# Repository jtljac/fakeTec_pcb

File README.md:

# fakeTec_pcb
My personal modification of the fakeTec, a low-cost nRF52 device with the form-factor of the Heltec v2, v3, & v4 devices 
compatible with [Meshtastic](https://meshtastic.org/)®.

This design is specifically based off of [Šimon Hořánek's](https://github.com/ShimonHoranek) 
[fakeTec V5 Rev. B](https://github.com/gargomoma/fakeTec_pcb/issues/24), licensed under 
[CERN-OHL-P-2.0](https://choosealicense.com/licenses/cern-ohl-p-2.0/).

Further inspiration has been taken from [Brian's Fork, the roTec](https://github.com/mofosyne/roTec_pcb), an alternative
board with greatly expanded wiring options and extra on-board guidence.

# Pictures
| Front                               | Back                              |
|:------------------------------------|:----------------------------------|
|  |  |

# Schematic
<details>
<summary>Schematic and component list</summary>
Note this list is for the v5.5.1

| Component Ref | Value     |
|:------------- |:--------- |
| C1, C2        | 100nf     |
| Q1, Q2, Q3    | AO3400A*  |
| R1, R2, R3    | 10K       |
| R4            | 680K      |
| R5            | 1M        |
| U1            | XB8089D0  |
| U2            | HT-RA62   |
| U3            | nice!nano |

\* Can be any SOT-23 logic level MOSFET that supports atleast 3v
</details>

## Features
- Small size based on Heltec v3: You can use the same cases!
- Lora with Heltec's HT-RA62
- Uses a [n!cenano](https://nicekeyboards.com/nice-nano/) or 
  [NRF52840 ProMicro](https://github.com/joric/nrfmicro/wiki/Alternatives#supermini-nrf52840l)
- BMS For low voltage cutout to prevent LiPo Overdraining
- Battery level sensing
- JST PH2.0mm connector for batteries
- I2C side ports ready to connect an OLED SSD1306 screen.
- Pads for connecting an encoder for canned messages
- A pad exposing P1.06 (38) for misc use
- Pads for connecting a serial GPS module
- MOSFETs for switching high current components
- 2mm mounting holes
- Mostly clear edges for mounting

## Modifications from fakeTec V5 Rev. B
- Cleaned up schematic
  - Changed Pins representing sides of MCUs to symbols fully representing said MCU
  - Changed labels to my preferred naming scheme
- Setup netclasses
- Shifted pads `P1.01`, `P1.02`, and `P1.07` to where I'm pretty sure they're supposed to be
  - I also added two sets as the NRF ProMicro and the Nice!Nano appear to have them in different places.
- Removed jumper for BMS
  - I will always install a BMS
- Removed jumper for GPS/FET1 Drain to FET1
  - Only one will be connected at a time, probably no difference if this is permanently connected to both
- Switched mosfets to AO3400A
  - I already have these and they're a drop in replacement
- Changed all resistors and Capacitors to 805 sized
  - I already have all the resistors in this size
- Removed debouncing capacitors and pull-up resistors from the buttons
  - [User mofosyne](https://github.com/mofosyne) provided evidence that it is unnecessary 
    [here](https://github.com/gargomoma/fakeTec_pcb/issues/64)
- Added ground pads to rotary encoder pads
- Added access to P1.06 for misc usage next to rotary encoder pads
- Changed battery connector to a JST PH-2.0mm
  - PH-2.0mm are also apparently more reliable
- Removed lots of silkscreen text
  - Don't need values or component names, just component references
  - Most of it was overlapping
- Moved BMS to side
  - Keeps it out the way of the battery connector
- Added a lot more stitching between front and back ground planes
- Removed vias from on top of silkscreen and off of pads
- Attempted to reduce layer crossings

# Firmware

| Version      | Lora Modules                     | Official Repo link                                                                                                                                          | Unofficial Repo link                                                                                                                                                                |
|:-------------|:---------------------------------|:------------------------------------------------------------------------------------------------------------------------------------------------------------|:------------------------------------------------------------------------------------------------------------------------------------------------------------------------------------|
| With TCXO    | EByte E22/E220-xxxM-22S/HT-RA62  | <a href="https://github.com/meshtastic/firmware/tree/master/variants/nrf52840/diy/nrf52_promicro_diy_tcxo" target="_blank">Official repo - With TCXO</a>    | <a href="https://github.com/mrekin/MeshtasticCustomBoards/tree/main/firmware/variants/nrf52840/diy/promicro_diy_m" target="_blank">With TCXO</a> @mrekin/MeshtasticCustomBoards     |
| Without TCXO | EByte E22/E220-xxxMM-22S/RA-01SH | <a href="https://github.com/meshtastic/firmware/tree/master/variants/nrf52840/diy/nrf52_promicro_diy_xtal" target="_blank">Official repo - Without TCXO</a> | <a href="https://github.com/mrekin/MeshtasticCustomBoards/tree/main/firmware/variants/nrf52840/diy/promicro_diy_mm" target="_blank">Without TCXO</a> @mrekin/MeshtasticCustomBoards |

> If you don't want to build your own image use <a href="https://flasher.meshtastic.org/" target="_blank">the official web flasher</a>. Select the `NRF52 Pro-micro DIY` under `Community Supported Devices` as your target device.

# Device Setup
After you've set up your device, there are a few things you can do in the config to tune it

## Battery ADC Multiplier
The default ADC multiplier for the DIY NRF52 Promicro firmware is slightly off at about `1.85`, due to this design using
a slightly differnt voltage divider, I found that mine is more accurate with a value of `1.68`.  
You should of course still tune yours further with https://meshtastic.org/docs/configuration/radio/power/#calibration-process-attribution

# Bill of materials
| Part                           | Source                                                                                                                                      | Note                                                                                                      |
|:-------------------------------|:--------------------------------------------------------------------------------------------------------------------------------------------|:----------------------------------------------------------------------------------------------------------|
| NRF52840 ProMicro or n!icenano | [AliExpress](https://www.aliexpress.com/item/1005006446457448.html)<br/> [niceKeyboards](https://nicekeyboards.com/nice-nano/#find-a-store) |[Please read it before buying red ProMicros](https://github.com/gargomoma/fakeTec_pcb/issues/30)           |
| HT-RA62                        | [Heltec](https://heltec.org/project/ht-ra62/)<br/> [AliExpress](https://www.aliexpress.com/item/1005005543917617.html)                      | I'd get it directly from heltec                                                                           |
| XB8089D0 BMS                   | [LCSC](https://www.lcsc.com/product-detail/C2760005.html)                                                                                   |                                                                                                           |
| 3x AO3400A MOSFETs             | [LCSC](https://www.lcsc.com/product-detail/C347475.html)<br/> [AliExpress](https://www.aliexpress.com/item/1005007115799728)                | Quite frankly, any logic level N-Channel MOSFET with a `SOT-23` footprint that takes at least 5v will do. |
| SMD JST PH2.0mm Socket         | [LCSC](https://www.lcsc.com/product-detail/C295747.html)<br/> [LCSC](https://www.lcsc.com/product-detail/C7429689.html)                     |                                                                                                           |
| SMD 805 Resistors              |                                                                                                                                             | You'll need 1x 1k, 3x 10K, 1x 680K, 1x 1M                                                                 |
| SMD 805 Ceramic Capacitors     |                                                                                                                                             | You'll need 2 x 100nF                                                                                     |
| 2x smd Button                  | [LCSC](https://www.lcsc.com/product-detail/C41427500.html)                                                                                  | You want something around 4 x 3 x 2                                                                       |
| OLED SSD1306 i2c (optional)    | [AliExpress](https://www.aliexpress.com/item/1005005970901119.html)                                                                         |                                                                                                           |
| Battery connection (optional)  | [AliExpress](https://www.aliexpress.com/item/1005002564191148.html)                                                                         | This is an example.                                                                                       |
| Glue Stick Sprint Antenna      | [AliExpress](https://www.aliexpress.com/item/1005008671071222.html)                                                                         |                                                                                                           |
| Antenna (Recommended           | [AliExpress](https://www.aliexpress.com/item/1005004607615001.html)                                                                         |                                                                                                           |
| Antenna pigtail (recommended)  | [AliExpress](https://www.aliexpress.com/item/4001287491018.html)                                                                            | It may underperformed with a cheap black pigtail.                                                         |
| PCB                            |                                                                                                                                             | Use your favourite company to get the PCB. I use [JLCPCB](https://jlcpcb.com/)                            |

# Troubleshooting
## Cannot write the firmware to the Microcontroller
It appears that many NRF ProMicros on AliExpress come with an older version of the bootloader which doesn't support
uf2 files that are larger than 512KB.
The steps to fix are detailed in [this github issue](https://github.com/meshtastic/firmware/issues/7091), of which were
taken from [this older FakeTec Guide](https://adrelien.com/blog/diy-meshtastic-how-to-build-your-own-meshtastic-device-with-faketec-pcb-nrf52840/#step-1-update-the-bootloader).  
They're also copied below for convenience:
1. Connect the node to your PC using a data cable
2. Put the node into DFU (Device Firmware Update) mode by shorting the GND and Reset pins once or twice, A new drive 
   should appear on your computer
3. Check the INFO_UF2.TXT file to determine your current bootloader version
4. Visit Adafruit's GitHub page for nRF52 Bootloader releases
5. Find the next release after your current version (you must update incrementally)
6. Download the nice_nano_bootloader-X.X.X.HEX and nice_nano_bootloader-X.X.X.UF2 files for your board
7. Drag and drop the .HEX file onto the drive first, then the .UF2 file
8. The device will disconnect and restart
9. Check the bootloader version again and repeat if necessary until you reach the latest version

My ProMicros arrived at version 6.0.0, and I only updated to 0.6.3 as it started working at that version and it looked
like a long process to go to the latest version.

## The Microcontroller isn't getting power/The microcontroller can't connect the battery/The microcontroller can't connect to the LoRa module/The buttons don't work
The micro controller is pretty difficult to solder to the pads through the through holes, it took me many attempts to
get it right.

Make sure you check each connection using a multimeter before you decide you've finished soldering.

If you're really struggling, you can use a fine file to turn the through holes into castellated edges.
 
Be careful though, fibreglass shards are not good for your lungs

## The battery isn't working
Double check which way round your battery connector is wired. The batteries I bought were wired the opposite way to the
connector on the board.

# About Meshtastic
[Meshtastic](https://meshtastic.org/)® is a registered trademark of Meshtastic LLC. Meshtastic software components are released under various licenses, see github for details.

# Disclaimer
No warranty is provided.
You use it at your own risk and take the responsibility upon yourself.

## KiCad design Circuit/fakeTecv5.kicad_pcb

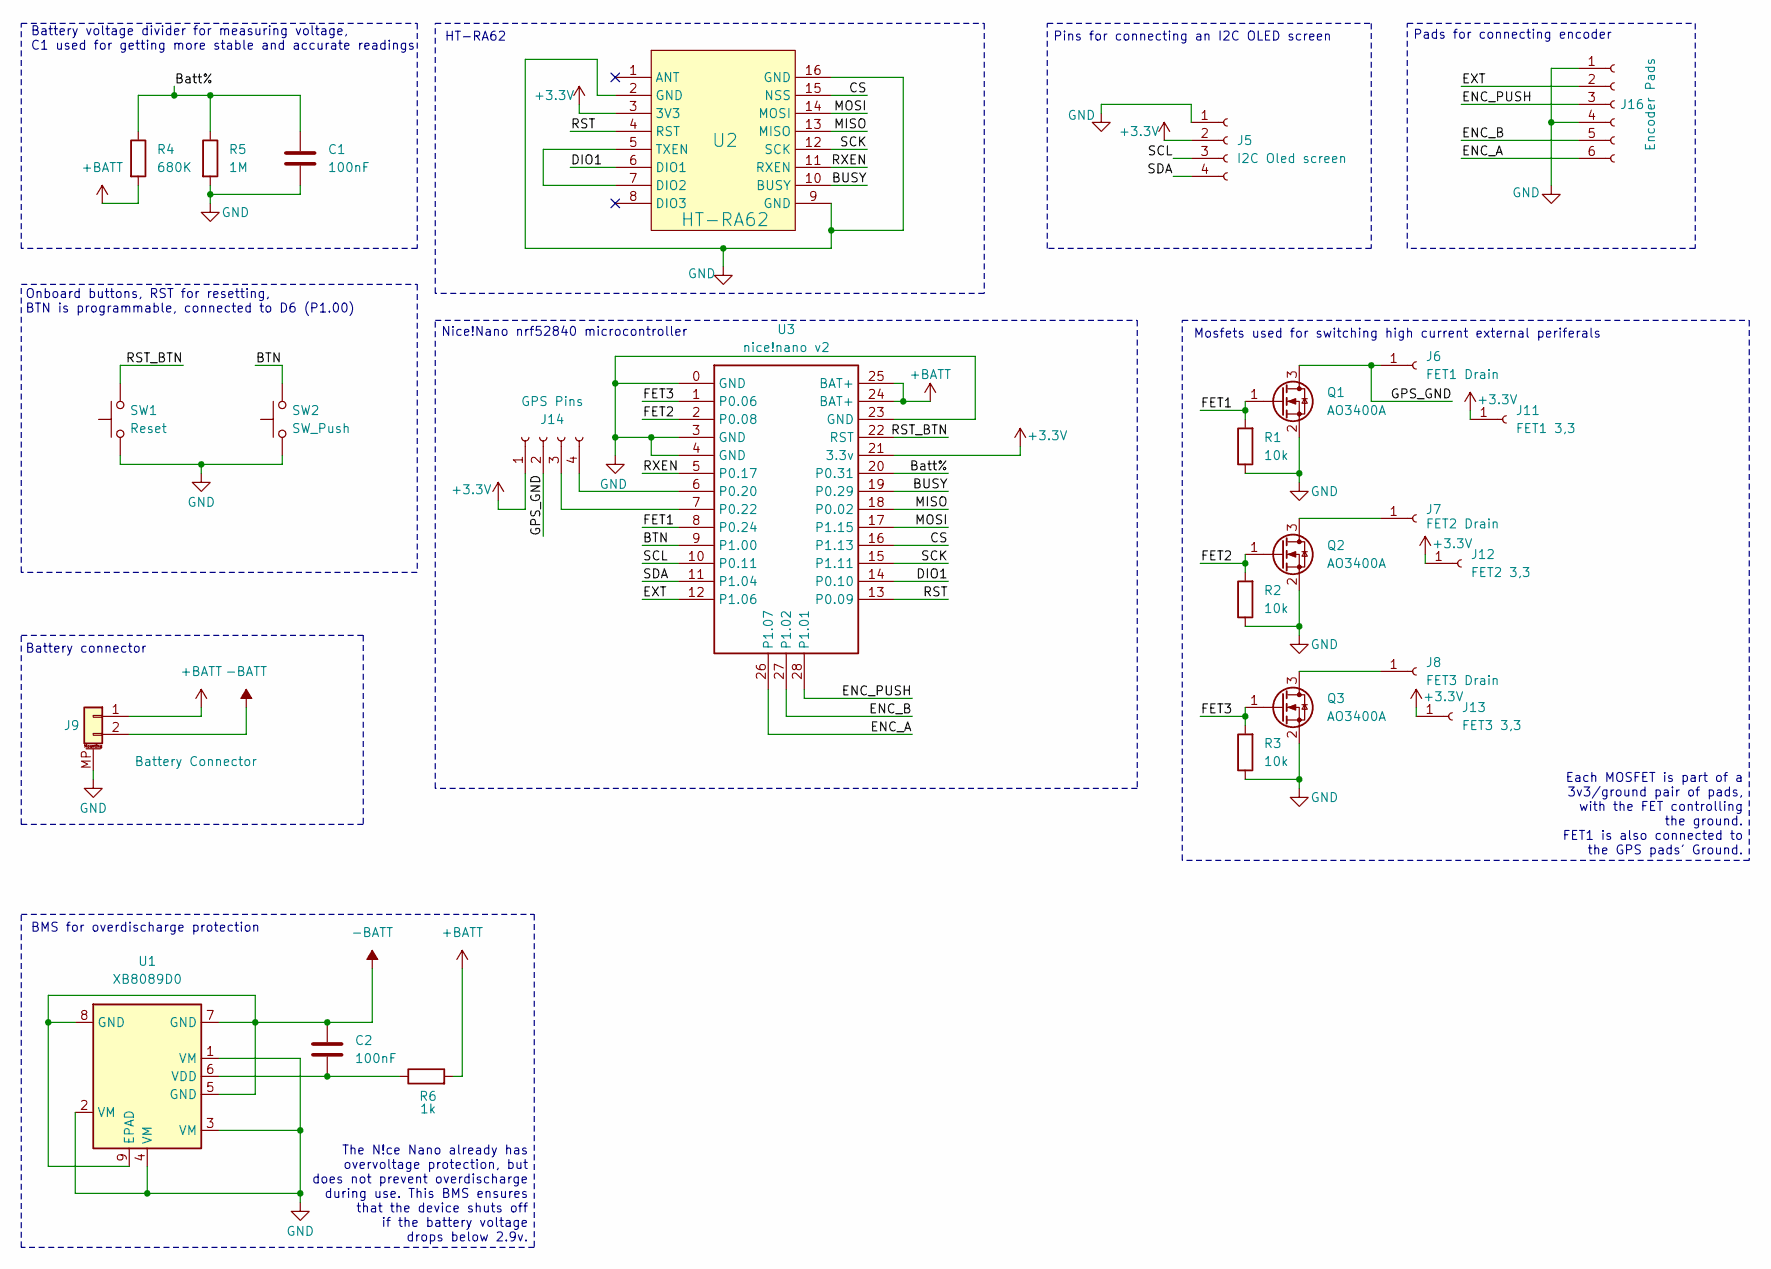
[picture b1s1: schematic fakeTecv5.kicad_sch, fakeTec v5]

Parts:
C1, C2: 100nF; C_0805_2012Metric_Pad1.18x1.45mm_HandSolder
J5: I2C Oled screen; PinHeader_1x04_P2.54mm_Vertical
J6: FET1 Drain; SMD_PAD_1x01
J7: FET2 Drain; SMD_PAD_1x01
J8: FET3 Drain; SMD_PAD_1x01
J9: Battery Connector; JST_PH_S2B-PH-SM4-TB_1x02-1MP_P2.00mm_Horizontal
J11: FET1 3,3; SMD_PAD_1x01
J12: FET2 3,3; SMD_PAD_1x01
J13: FET3 3,3; SMD_PAD_1x01
J14: GPS Pins; SMD_PAD_1x04
J16: Encoder Pads; SMD_PAD_1x06
Q1, Q2, Q3: AO3400A; SOT-23_Handsoldering
R1, R2, R3: 10k; R_0805_2012Metric_Pad1.20x1.40mm_HandSolder
R4: 680K; R_0805_2012Metric_Pad1.20x1.40mm_HandSolder
R5: 1M; R_0805_2012Metric_Pad1.20x1.40mm_HandSolder
R6: 1k; R_0805_2012Metric_Pad1.20x1.40mm_HandSolder
SW1: Reset; SW_Push_SPST_NO_Alps_SKRK
SW2: SW_Push; SW_Push_SPST_NO_Alps_SKRK
U1: XB8089D0; SOIC-8-1EP_3.9x4.9mm_P1.27mm_EP2.41x3.3mm
U2: HT-RA62
U3: nice!nano v2; NICE!NANO V2_2 SMD

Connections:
+3.3V: J5.2, J11.1, J12.1, J13.1, J14.1, U2.3 (3V3), U3.21 (3.3v)
+BATT: J9.1, R4.2, R6.2, U3.24 (BAT+), U3.25 (BAT+)
-BATT: C2.1, J9.2, U1.5 (GND), U1.7 (GND), U1.8 (GND), U1.9 (EPAD)
/BTN: SW2.2, U3.9 (P1.00)
/BUSY: U2.10 (BUSY), U3.19 (P0.29)
/Batt%: C1.1, R4.1, R5.1, U3.20 (P0.31)
/CS: U2.15 (NSS), U3.16 (P1.13)
/DIO1: U2.6 (DIO1), U3.14 (P0.10)
/ENC_A: J16.6, U3.26 (P1.07)
/ENC_B: J16.5, U3.27 (P1.02)
/ENC_PUSH: J16.3, U3.28 (P1.01)
/EXT: J16.2, U3.12 (P1.06)
/FET1: Q1.1 (G), R1.2, U3.8 (P0.24)
/FET2: Q2.1 (G), R2.2, U3.2 (P0.08)
/FET3: Q3.1 (G), R3.2, U3.1 (P0.06)
/GPS_GND: J6.1, J14.2, Q1.3 (D)
/MISO: U2.13 (MISO), U3.18 (P0.02)
/MOSI: U2.14 (MOSI), U3.17 (P1.15)
/RST: U2.4 (RST), U3.13 (P0.09)
/RST_BTN: SW1.2, U3.22 (RST)
/RXEN: U2.11 (RXEN), U3.5 (P0.17)
/SCK: U2.12 (SCK), U3.15 (P1.11)
/SCL: J5.3, U3.10 (P0.11)
/SDA: J5.4, U3.11 (P1.04)
GND: C1.2, J5.1, J9.MP (MountPin), J16.1, J16.4, Q1.2 (S), Q2.2 (S), Q3.2 (S), R1.1, R2.1, R3.1, R5.2, SW1.1, SW2.1, U1.1 (VM), U1.2 (VM), U1.3 (VM), U1.4 (VM), U2.2 (GND), U2.9 (GND), U2.16 (GND), U3.0 (GND), U3.3 (GND), U3.4 (GND), U3.23 (GND)
unnamed: J7.1, Q2.3 (D)
unnamed: J8.1, Q3.3 (D)
unnamed: J14.3, U3.7 (P0.22)
unnamed: J14.4, U3.6 (P0.20)
unnamed: C2.2, R6.1, U1.6 (VDD)
unnamed: U2.5 (TXEN), U2.7 (DIO2)

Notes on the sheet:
Nice!Nano nrf52840 microcontroller
Pads for connecting encoder
Mosfets used for switching high current external periferals
The N!ce Nano already has overvoltage protection, but does not prevent overdischarge during use. This BMS ensures that the device shuts off if the battery voltage drops below 2.9v.
BMS for overdischarge protection
Battery voltage divider for measuring voltage, C1 used for getting more stable and accurate readings
HT-RA62
Onboard buttons, RST for resetting, BTN is programmable, connected to D6 (P1.00)
Battery connector
Each MOSFET is part of a 3v3/ground pair of pads, with the FET controlling the ground. FET1 is also connected to the GPS pads' Ground.
Pins for connecting an I2C OLED screen

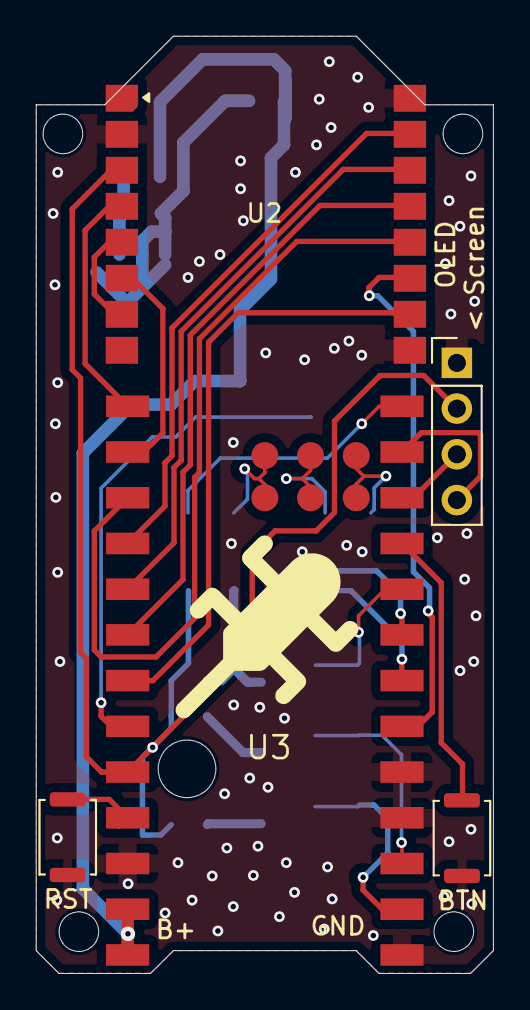
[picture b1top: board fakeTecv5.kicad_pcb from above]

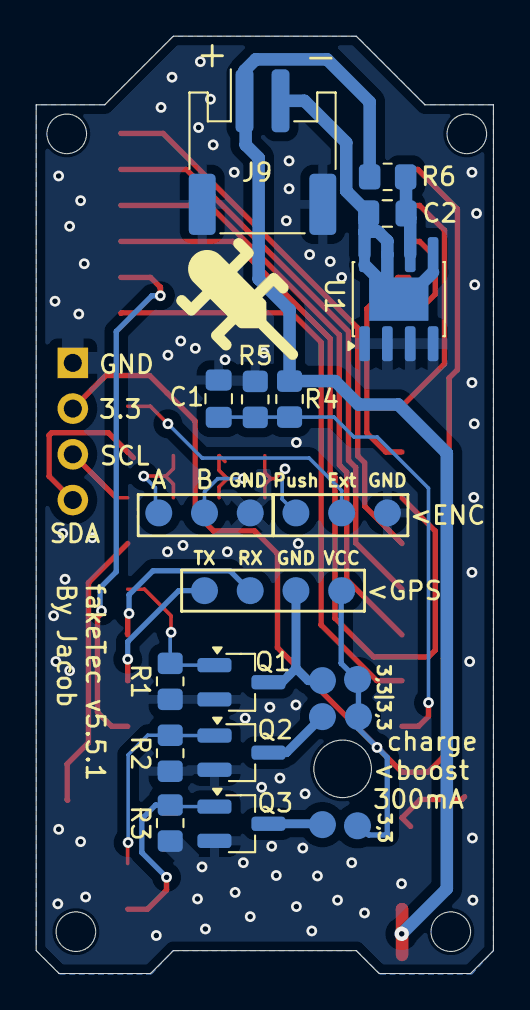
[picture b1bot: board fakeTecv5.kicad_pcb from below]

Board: 2 copper layers, 25.4 x 52.1 mm, 26 parts (21 on the bottom side), 31 nets.

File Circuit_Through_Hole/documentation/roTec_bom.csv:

"Reference","Qty","Package","Value","Description","MPD","MPL","Datasheet","Shopping","Manufacturer","MPN"
"BZ1","1","SMD,5x5mm","Buzzer 5020","Buzzer, polarized","75dB 4kHz 3V SMD,5x5mm Alarms, Buzzers, and Sirens RoHS","https://www.lcsc.com/product-detail/C7544810.html?s_z=n_buzz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","https://www.lcsc.com/datasheet/C7544810.pdf","https://www.lcsc.com/search?q=Buzzer_5020&s_z=n_Buzzer_5020","HYDZ","HYG-5020A"
"C2","1","0805","100nF","Unpolarized capacitor","","","~","https://www.lcsc.com/search?q=100nF%25200805&s_z=n_100nF%25200805","",""
"J9","1","SMD,P=1.25mm,Surface Mount,Right Angle","Molex PicoBlade 0532610271","1.25mm Pitch, PicoBlade PCB Header, Single Row, Right-Angle, Surface Mount, Tin (Sn) Plating, Friction Lock, 2 Circuits, Natural, Tape and Reel","Connector Header 2 position 1.25mm Pitch","https://www.lcsc.com/product-detail/C225111.html","https://www.molex.com/content/dam/molex/molex-dot-com/produc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","https://www.lcsc.com/search?q=0532610271&s_z=n_0532610271","CJT(Changjiang Connectors)","A1251WR-S-2P"
"J38,J50","2","SMD,P=1mm,Surface Mount,Right Angle","JST-SH-4","Generic connectable mounting pin connector, single row, 01x04, script generated (kicad-library-utils/schlib/autogen/connector/)","4P 1x4P Tin 1mm 50V 4 1A 1 Surface Mount, Right Angle -25℃~+85℃ SMD,P=1mm,Surface Mount,Right Angle Headers, Male Pins RoHS","https://www.lcsc.com/product-detail/C51940130.html?s_z=n_SM0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","https://www.jst-mfg.com/product/pdf/eng/eSH.pdf","https://www.lcsc.com/search?q=SM04B-SRSS-TB&s_z=n_SM04B-SRSS-TB","JST Sales America Inc.","SM04B-SRSS-TB"
"M1","1","Wire Leads","ERM Motor","VIBRATION ERM MOTOR 3V","DC Motor Vibration, ERM (Haptic) 3VDC","https://www.digikey.com.au/en/products/detail/seeed-technolo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","https://mm.digikey.com/Volume0/opasdata/d220001/medias/docus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","https://www.digikey.com.au/short/332zpfdb","Seeed Technology Co., Ltd","316040001"
"OLED1","1","Through Hole","I2C OLED Module","I2C OLED Module With Header pin space 2.54mm","0.96 Inch OLED Display Module I2C IIC SPI Serial 128X64 SSD1306 LCD 3.3-5V 4 Pin White/Blue/Yellow Blue for Arduino","https://www.aliexpress.com/item/1005008738379315.html","https://cdn-shop.adafruit.com/datasheets/SSD1306.pdf","https://www.aliexpress.com/w/wholesale-0.96-Inch-OLED-Displa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","",""
"Q1-Q3","3","SOT-23-3L","AO3400A","30V Vds, 5.7A Id, N-Channel MOSFET, SOT-23","30V 5.7A 48mΩ@2.5V 1.4W SOT-23-3L Single FETs, MOSFETs RoHS","https://www.lcsc.com/product-detail/C20917.html?s_z=n_AO3400A","http://www.aosmd.com/pdfs/datasheet/AO3400A.pdf","https://www.lcsc.com/search?q=MOSFET%2520N-CH%2520SOT-23-3L&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","Alpha & Omega Semiconductor Inc.","AO3400A"
"R1-R3","3","0805","10k","Resistor","","","~","https://www.lcsc.com/search?q=10K%25200805&s_z=n_10K%25200805","",""
"R4","1","0805","680K","Resistor","","","~","https://www.lcsc.com/search?q=680K%25200805&s_z=n_680K%25200805","",""
"R5","1","0805","1.0M","Resistor","","","~","https://www.lcsc.com/search?q=1M%25200805&s_z=n_1M%25200805","",""
"R6","1","0805","1k","Resistor","","","~","https://www.lcsc.com/search?q=1k%25200805&s_z=n_1k%25200805","",""
"SW1","1","SMD,4x3mm","Reset","Push button switch, generic, two pins","Without Bracket 3.9mm 12V 2.93mm Round Button SPST 50mA SMD,4x3mm Tactile Switches RoHS","https://www.lcsc.com/product-detail/C455280.html?s_z=n_TS-10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","https://www.lcsc.com/datasheet/C455280.pdf","https://www.lcsc.com/search?q=TS-1088R-02026&s_z=n_TS-1088R-02026","XUNPU","TS-1088R-02026"
"SW2","1","SMD,4x3mm","SW_Push","Push button switch, generic, two pins","Without Bracket 3.9mm 12V 2.93mm Round Button SPST 50mA SMD,4x3mm Tactile Switches RoHS","https://www.lcsc.com/product-detail/C455280.html?s_z=n_TS-10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","https://www.lcsc.com/datasheet/C455280.pdf","https://www.lcsc.com/search?q=TS-1088R-02026&s_z=n_TS-1088R-02026","XUNPU","TS-1088R-02026"
"SW3","1","EC11","RotaryEncoder_Switch","Rotary encoder, dual channel, incremental quadrate outputs, with switch","EC11 horizontal rotary encoder Plum blossom shaft With switch 15/20mm 5PIN 20bit pulse digital potentiometer With knob cap","https://www.aliexpress.com/item/1005010398201852.html or https://www.digikey.com.au/en/products/detail/same-sky-forme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","https://www.cuidevices.com/product/resource/acz11.pdf","https://www.aliexpress.com/w/wholesale-rotary-encoder-EC11-h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 or https://www.digikey.com.au/short/7v5m7j9j","Same Sky (Formerly CUI Devices)","ACZ11BR1E-15KQA1-12C"
"U1","1","SOIC-8","XB8089D0","2.9V~6V Lithium-ion/Polymer 1 SOP-8-EP Battery Management ROHS","One Cell Lithium-ion/Polymer Battery Protection IC","https://www.lcsc.com/product-detail/C2760005.html?s_z=n_XySe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","https://www.lcsc.com/datasheet/lcsc_datasheet_2410121637_XyS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","https://www.lcsc.com/search?q=XB8089D0&s_z=n_XB8089D0","XySemi","XB8089D0"
"U2","1","HT-RA62","HT-RA62","The Heltec LoRa Series Module HT-RA62 was designed and developed by Heltec Automation.","HT-RA62 Module SX1262 Secondary Development Supports LoRaWAN Protocol Heltec","https://www.aliexpress.com/item/1005005543917617.html","https://resource.heltec.cn/download/HT-RA62/HT-RA62(Rev1.1).pdf","https://www.aliexpress.com/w/wholesale-HT%2525252dRA62.html","Heltec","HT-RA62"
"U3","1","nice!nano v2","nice!nano v2","NRF52840 Development Board","Pro NRF52840 Development Board Compatible with Nice!Nano V2.0 Bluetooth Charging Management Pro Micro NRF52840","https://www.aliexpress.com/item/1005010222966695.html","https://nicekeyboards.com/docs/nice-nano/pinout-schematic","https://www.aliexpress.com/w/wholesale-NRF52840-1%2525252d10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","Nice!","nice!nano v2"

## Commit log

2025-11-11 Clarified firmware instructions
2025-11-24 Added pads for nice!nano and nrf promicro, more deco, more justifications
2025-12-15 use alignment hole
2025-12-15 adjust extra testpoint to the side of oled screen
2025-12-15 move text
2025-12-18 hw: modify power connector to support both JST GH and PH connector
2025-12-18 hw: refactor spi routing. Make OLED screen pins friction fit
    SPI is likely running under 50mHz mark so vias is not an issue and want to keep signal path small. Made careful note to keep all spi lines under the ground plane as much as possible.
2025-12-21 Drop files from .gitignore
2025-12-21 hw: fix incorrect label on nice!nano symbol and adjust schematic.
    This effects the encoder controls. No change to pcb required.
2025-12-21 hw: Adjust gitignore
2025-12-21 hw: Thicker lines. All 0.2 lines converted to 0.3mm
2025-12-21 hw: Add additional notes on platform io GPIO mapping references
2025-12-21 hw: Buzzer is wired incorrectly. Fixed wiring and updated schematic and pcb
2025-12-21 hw: update preview image
2025-12-22 hw: Battery connector clarification
    Heltec LoRa32 is using Molex Picoblade... not JST
2025-12-24 hw: Update schematic and connector to clarify battery connector
    Including some photos and directions on locating the correct parts
2025-12-24 hw: Text Variable. Also mark as Rev5.
2025-12-26 hw: Add JST-SH-4 for encoder. Marked as Rev5.1
2025-12-26 hw: Add GPS slot and mark as Rev5.2
2025-12-26 hw: silkscreen correction to ENC_PUSH. Marked as Rev5.2.1
2025-12-26 hw: optimise ground plane and add silkscreen to battery header. Mark as Rev5.2.2
2025-12-27 improved documentation
2025-12-27 shorter bom table
2025-12-27 minor changes to readme
2025-12-27 readme adjust for more compact BOM
2025-12-27 BOM tips
2025-12-27 Added extra readme content having now built the faketec
2025-12-29 hw: Fix silkscreen 680KΩ (Previously 680Ω)
2025-12-29 readme update
2025-12-29 hw: change footprint to rely on testpads on the nice!nano footprint instead
2025-12-29 hw: Add makefile. Refine. Rev5.3
2025-12-29 image not required anymore
2025-12-29 hw: Added a roTecTH through hole version
    Experimental
2025-12-29 sub readmes
2025-12-29 Update schematic and readme
2025-12-30 hw: refinement to roTecTH
2025-12-30 readme updated
2025-12-30 hw: mark roTecTH as Rev5.4 . Fix trace too close DRC error
2026-01-03 Added space to edge of board, removed pull up resistors and debouncing capacitors, added access to extra pin
    Inspiration taken from fork: https://github.com/mofosyne/roTec_pcb.
2026-01-03 Added extra context to roTec inclusion in readme
2026-02-08 Fix bad castellated image in readme
2026-02-20 Added schematic and component references to readme
